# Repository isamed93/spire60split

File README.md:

# spire60split
This is the repo for a 60% low profile split keyboard.

## Key sizing
Sizes included in choc layouts:
* pipe and tab are 1.5U
* caps is 1.75U
* backspace is 2U
Sizes not included in choc layouts:
* enter and left shift are 2.25U
* right shift is 2.75

## Layout
Layout was designed in http://www.keyboard-layout-editor.com/#/ and then imported the raw data from there onto https://builder.mrkeebs.com/ where the pcb file for KiCad was downloaded.

The layout information can be found inside the layout folder.

### Split layout
QMK documentation for split keyboards can be found here https://github.com/qmk/qmk_firmware/blob/master/docs/feature_split_keyboard.md

## Firmware
Firmware was coded following this guide: https://github.com/DIYCharles/DIYKeyboards#qmk-firmware

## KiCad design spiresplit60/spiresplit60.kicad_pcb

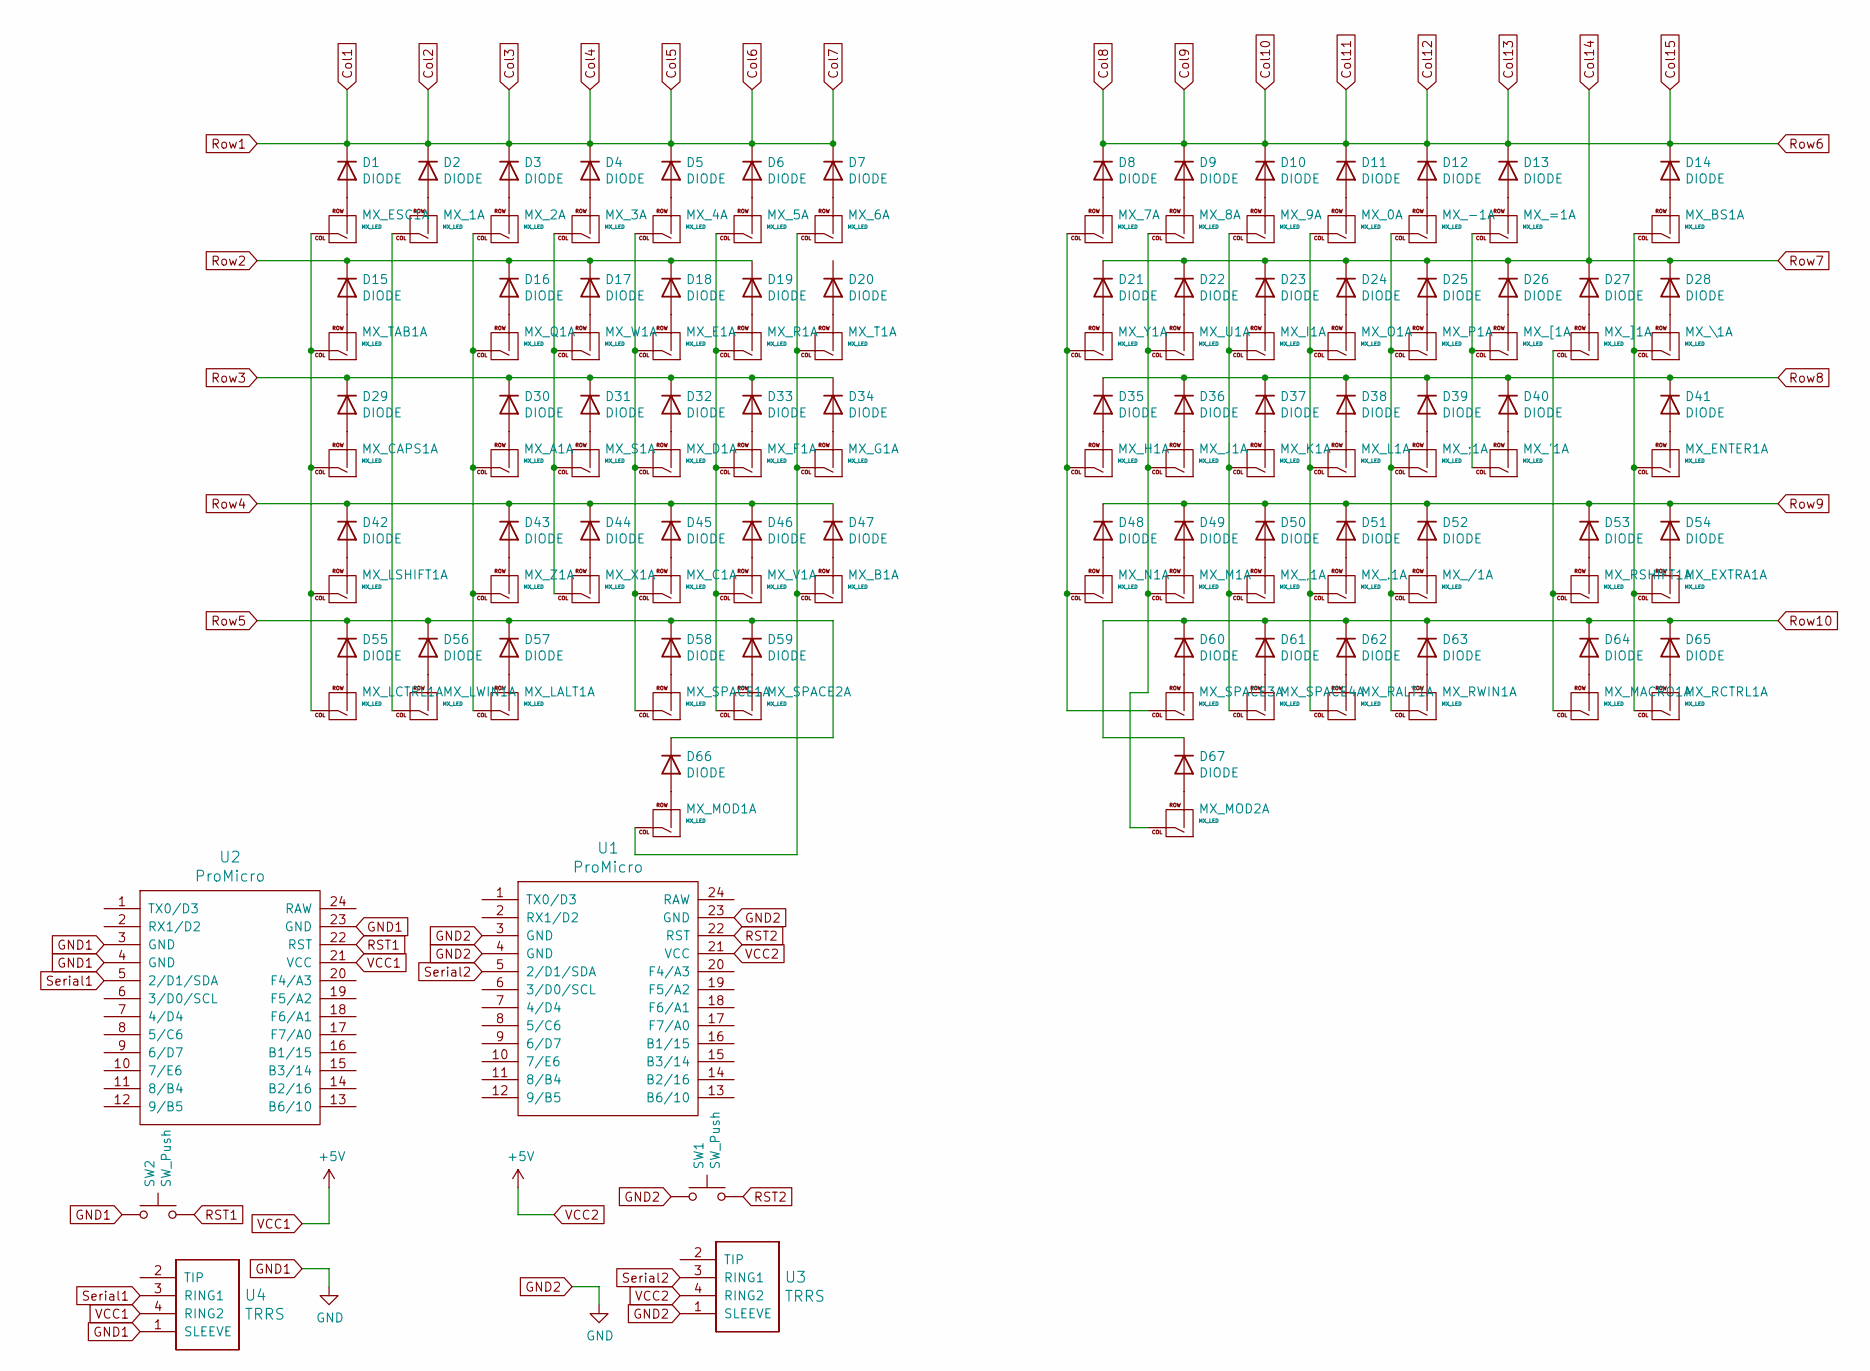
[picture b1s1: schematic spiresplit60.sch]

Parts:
D1, D2, D3, D4, D5, D6, D7, D8, D9, D10, D11, D12, D13, D14, D15, D16, D17, D18, D19, D20, D21, D22, D23, D24, D25, D26, D27, D28, D29, D30, D31, D32, D33, D34, D35, D36, D37, D38, D39, D40, D41, D42, D43, D44, D45, D46, D47, D48, D49, D50, D51, D52, D53, D54, D55, D56, D57, D58, D59, D60, D61, D62, D63, D64, D65, D66, D67: DIODE; D_SOD-123
MX_0, MX_1, MX_2, MX_3, MX_4, MX_5, MX_6, MX_7, MX_8, MX_9, MX_.1: MX_LED; Kailh-PG1350-1u
MX_'1: MX_LED; Kailh-PG1350-1u
MX_,1: MX_LED; Kailh-PG1350-1u
MX_-1: MX_LED; Kailh-PG1350-1u
MX_/1: MX_LED; Kailh-PG1350-1u
MX_;1: MX_LED; Kailh-PG1350-1u
MX_=1: MX_LED; Kailh-PG1350-1u
MX_A1: MX_LED; Kailh-PG1350-1u
MX_B1: MX_LED; Kailh-PG1350-1u
MX_BS1: MX_LED; Kailh-PG1350-1u
MX_C1: MX_LED; Kailh-PG1350-1u
MX_CAPS1: MX_LED; Kailh-PG1350-1u
MX_D1: MX_LED; Kailh-PG1350-1u
MX_E1: MX_LED; Kailh-PG1350-1u
MX_ENTER1: MX_LED; Kailh-PG1350-1u
MX_ESC1: MX_LED; Kailh-PG1350-1u
MX_EXTRA1: MX_LED; Kailh-PG1350-1u
MX_F1: MX_LED; Kailh-PG1350-1u
MX_G1: MX_LED; Kailh-PG1350-1u
MX_H1: MX_LED; Kailh-PG1350-1u
MX_I1: MX_LED; Kailh-PG1350-1u
MX_J1: MX_LED; Kailh-PG1350-1u
MX_K1: MX_LED; Kailh-PG1350-1u
MX_L1: MX_LED; Kailh-PG1350-1u
MX_LALT1: MX_LED; Kailh-PG1350-1u
MX_LCTRL1: MX_LED; Kailh-PG1350-1u
MX_LSHIFT1: MX_LED; Kailh-PG1350-1u
MX_LWIN1: MX_LED; Kailh-PG1350-1u
MX_M1: MX_LED; Kailh-PG1350-1u
MX_MACRO1: MX_LED; Kailh-PG1350-1u
MX_MOD1, MX_MOD2: MX_LED; Kailh-PG1350-1u
MX_N1: MX_LED; Kailh-PG1350-1u
MX_O1: MX_LED; Kailh-PG1350-1u
MX_P1: MX_LED; Kailh-PG1350-1u
MX_Q1: MX_LED; Kailh-PG1350-1u
MX_R1: MX_LED; Kailh-PG1350-1u
MX_RALT1: MX_LED; Kailh-PG1350-1u
MX_RCTRL1: MX_LED; Kailh-PG1350-1u
MX_RSHIFT1: MX_LED; Kailh-PG1350-1u
MX_RWIN1: MX_LED; Kailh-PG1350-1u
MX_S1: MX_LED; Kailh-PG1350-1u
MX_SPACE1, MX_SPACE2, MX_SPACE3, MX_SPACE4: MX_LED; Kailh-PG1350-1u
MX_T1: MX_LED; Kailh-PG1350-1u
MX_TAB1: MX_LED; Kailh-PG1350-1u
MX_U1: MX_LED; Kailh-PG1350-1u
MX_V1: MX_LED; Kailh-PG1350-1u
MX_W1: MX_LED; Kailh-PG1350-1u
MX_X1: MX_LED; Kailh-PG1350-1u
MX_Y1: MX_LED; Kailh-PG1350-1u
MX_Z1: MX_LED; Kailh-PG1350-1u
MX_[1: MX_LED; Kailh-PG1350-1u
MX_\1: MX_LED; Kailh-PG1350-1u
MX_]1: MX_LED; Kailh-PG1350-1u
SW1, SW2: SW_Push; SW_SPST_TL3342
U1, U2: ProMicro; ProMicro_v3
U3, U4: TRRS; TRRS-PJ-320A

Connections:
Col1: D1.2 (K), D2.2 (K), D3.2 (K), D4.2 (K), D5.2 (K), D6.2 (K), D7.2 (K)
Col10: D8.2 (K), D9.2 (K), D10.2 (K), D11.2 (K), D12.2 (K), D13.2 (K), D14.2 (K)
Col14: D21.2 (K), D22.2 (K), D23.2 (K), D24.2 (K), D25.2 (K), D26.2 (K), D27.2 (K), D28.2 (K)
GND1: SW1.1, SW2.1, U1.3 (GND), U1.4 (GND), U1.23 (GND), U2.3 (GND), U2.4 (GND), U2.23 (GND), U3.1 (SLEEVE), U4.1 (SLEEVE)
unnamed: D1.1 (A), MX_ESC1.2 (ROW)
unnamed: D2.1 (A), MX_1.2 (ROW)
unnamed: D3.1 (A), MX_2.2 (ROW)
unnamed: D4.1 (A), MX_3.2 (ROW)
unnamed: D5.1 (A), MX_4.2 (ROW)
unnamed: D6.1 (A), MX_5.2 (ROW)
unnamed: D7.1 (A), MX_6.2 (ROW)
unnamed: D8.1 (A), MX_7.2 (ROW)
unnamed: D9.1 (A), MX_8.2 (ROW)
unnamed: D10.1 (A), MX_9.2 (ROW)
unnamed: D11.1 (A), MX_0.2 (ROW)
unnamed: D12.1 (A), MX_-1.2 (ROW)
unnamed: D13.1 (A), MX_=1.2 (ROW)
unnamed: D14.1 (A), MX_BS1.2 (ROW)
unnamed: D15.1 (A), MX_TAB1.2 (ROW)
unnamed: D16.1 (A), MX_Q1.2 (ROW)
unnamed: D17.1 (A), MX_W1.2 (ROW)
unnamed: D18.1 (A), MX_E1.2 (ROW)
unnamed: D19.1 (A), MX_R1.2 (ROW)
unnamed: D20.1 (A), MX_T1.2 (ROW)
unnamed: D21.1 (A), MX_Y1.2 (ROW)
unnamed: D22.1 (A), MX_U1.2 (ROW)
unnamed: D23.1 (A), MX_I1.2 (ROW)
unnamed: D24.1 (A), MX_O1.2 (ROW)
unnamed: D25.1 (A), MX_P1.2 (ROW)
unnamed: D26.1 (A), MX_[1.2 (ROW)
unnamed: D27.1 (A), MX_]1.2 (ROW)
unnamed: D28.1 (A), MX_\1.2 (ROW)
unnamed: D29.1 (A), MX_CAPS1.2 (ROW)
unnamed: D30.1 (A), MX_A1.2 (ROW)
unnamed: D31.1 (A), MX_S1.2 (ROW)
unnamed: D32.1 (A), MX_D1.2 (ROW)
unnamed: D33.1 (A), MX_F1.2 (ROW)
unnamed: D34.1 (A), MX_G1.2 (ROW)
unnamed: D35.1 (A), MX_H1.2 (ROW)
unnamed: D36.1 (A), MX_J1.2 (ROW)
unnamed: D37.1 (A), MX_K1.2 (ROW)
unnamed: D38.1 (A), MX_L1.2 (ROW)
unnamed: D39.1 (A), MX_;1.2 (ROW)
unnamed: D40.1 (A), MX_'1.2 (ROW)
unnamed: D41.1 (A), MX_ENTER1.2 (ROW)
unnamed: D42.1 (A), MX_LSHIFT1.2 (ROW)
unnamed: D43.1 (A), MX_Z1.2 (ROW)
unnamed: D44.1 (A), MX_X1.2 (ROW)
unnamed: D45.1 (A), MX_C1.2 (ROW)
unnamed: D46.1 (A), MX_V1.2 (ROW)
unnamed: D47.1 (A), MX_B1.2 (ROW)
unnamed: D48.1 (A), MX_N1.2 (ROW)
unnamed: D49.1 (A), MX_M1.2 (ROW)
unnamed: D50.1 (A), MX_,1.2 (ROW)
unnamed: D51.1 (A), MX_.1.2 (ROW)
unnamed: D52.1 (A), MX_/1.2 (ROW)
unnamed: D53.1 (A), MX_RSHIFT1.2 (ROW)
unnamed: D54.1 (A), MX_EXTRA1.2 (ROW)
unnamed: D55.1 (A), MX_LCTRL1.2 (ROW)
unnamed: D56.1 (A), MX_LWIN1.2 (ROW)
unnamed: D57.1 (A), MX_LALT1.2 (ROW)
unnamed: D58.1 (A), MX_SPACE1.2 (ROW)
unnamed: D59.1 (A), MX_SPACE2.2 (ROW)
unnamed: D60.1 (A), MX_SPACE3.2 (ROW)
unnamed: D61.1 (A), MX_SPACE4.2 (ROW)
unnamed: D62.1 (A), MX_RALT1.2 (ROW)
unnamed: D63.1 (A), MX_RWIN1.2 (ROW)
unnamed: D64.1 (A), MX_MACRO1.2 (ROW)
unnamed: D65.1 (A), MX_RCTRL1.2 (ROW)
unnamed: D66.1 (A), MX_MOD1.2 (ROW)
unnamed: D67.1 (A), MX_MOD2.2 (ROW)
unnamed: MX_1.1 (COL), MX_LWIN1.1 (COL)
unnamed: MX_2.1 (COL), MX_A1.1 (COL), MX_LALT1.1 (COL), MX_Q1.1 (COL), MX_Z1.1 (COL)
unnamed: MX_3.1 (COL), MX_S1.1 (COL), MX_W1.1 (COL), MX_X1.1 (COL)
unnamed: MX_4.1 (COL), MX_C1.1 (COL), MX_D1.1 (COL), MX_E1.1 (COL), MX_SPACE1.1 (COL)
unnamed: MX_5.1 (COL), MX_F1.1 (COL), MX_R1.1 (COL), MX_SPACE2.1 (COL), MX_V1.1 (COL)
unnamed: MX_6.1 (COL), MX_B1.1 (COL), MX_G1.1 (COL), MX_MOD1.1 (COL), MX_T1.1 (COL)
unnamed: MX_7.1 (COL), MX_H1.1 (COL), MX_N1.1 (COL), MX_SPACE3.1 (COL), MX_Y1.1 (COL)
unnamed: MX_8.1 (COL), MX_J1.1 (COL), MX_M1.1 (COL), MX_MOD2.1 (COL), MX_U1.1 (COL)
unnamed: MX_'1.1 (COL), MX_=1.1 (COL), MX_[1.1 (COL)
unnamed: MX_9.1 (COL), MX_,1.1 (COL), MX_I1.1 (COL), MX_K1.1 (COL), MX_SPACE4.1 (COL)
unnamed: MX_-1.1 (COL), MX_/1.1 (COL), MX_;1.1 (COL), MX_P1.1 (COL), MX_RWIN1.1 (COL)
unnamed: MX_0.1 (COL), MX_.1.1 (COL), MX_L1.1 (COL), MX_O1.1 (COL), MX_RALT1.1 (COL)
unnamed: MX_BS1.1 (COL), MX_ENTER1.1 (COL), MX_EXTRA1.1 (COL), MX_RCTRL1.1 (COL), MX_\1.1 (COL)
unnamed: MX_CAPS1.1 (COL), MX_ESC1.1 (COL), MX_LCTRL1.1 (COL), MX_LSHIFT1.1 (COL), MX_TAB1.1 (COL)
unnamed: MX_MACRO1.1 (COL), MX_RSHIFT1.1 (COL), MX_]1.1 (COL)
RST1: SW2.2, U2.22 (RST)
RST2: SW1.2, U1.22 (RST)
Row2: D15.2 (K), D16.2 (K), D17.2 (K), D18.2 (K), D19.2 (K)
Row3: D29.2 (K), D30.2 (K), D31.2 (K), D32.2 (K), D33.2 (K), D34.2 (K)
Row4: D42.2 (K), D43.2 (K), D44.2 (K), D45.2 (K), D46.2 (K), D47.2 (K)
Row5: D55.2 (K), D56.2 (K), D57.2 (K), D58.2 (K), D59.2 (K), D66.2 (K)
Row8: D35.2 (K), D36.2 (K), D37.2 (K), D38.2 (K), D39.2 (K), D40.2 (K), D41.2 (K)
Row9: D48.2 (K), D49.2 (K), D50.2 (K), D51.2 (K), D52.2 (K), D53.2 (K), D54.2 (K)
Row10: D60.2 (K), D61.2 (K), D62.2 (K), D63.2 (K), D64.2 (K), D65.2 (K), D67.2 (K)
Serial1: U2.5 (2/D1/SDA), U4.3 (RING1)
Serial2: U1.5 (2/D1/SDA), U3.3 (RING1)
VCC1: U1.21 (VCC), U2.21 (VCC), U3.4 (RING2), U4.4 (RING2)

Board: 2 copper layers, 140 parts (69 on the bottom side), 98 nets, no tracks yet.

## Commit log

2022-09-13 Added and removed keebio-parts.pretty as a submodule
2022-09-13 Added library submodules
2022-09-13 Added further information on how to design things
2022-09-13 Added keyboard layout design obtained from the websites detailed in the README.md
2022-09-13 KiCad project for the keyboard. Added all the switches in the schematic
2022-09-13 Template ignore file for KiCad projects
2022-09-16 Placed all switches and switch diodes
2022-09-18 idk lol
2022-09-18 idek what is going on with the lib
2022-09-18 Restarting submodules libraries
2022-09-19 Added submodules to a different folder
2022-09-19 Finished edge cuts
